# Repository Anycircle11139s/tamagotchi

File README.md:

# tamagotchi
I made a custom tamagotchi for myself because stasis is taking forever to send the tamagotchis and I lowkey gotta improve my responsibility. I followed the guided tutorial from fallout and looked at some other projects for reference. Overall I am really happy with my progress and I learnt a decent amount about PCBs while retaining/honing my CADing skills. The schematic and PCB were fairly easy for me, but when creating the pcb, I decided on makeing the weirdest shape in existence, so I had to spend a really long time matching the PCB shape for the CAD case. The journals and other info can be found on my stasis project (https://stasis.hackclub.com/dashboard/projects/cmoldt6hz000401o6fho5nhdl)
<br>

<br>

<br>

<br>

<br>

<br>

<br>
<br>

# BOM
<br>

|Name            |Purpose                                           |Quantity|Total Cost (USD)|Link                                                                                                                                                                                                                                                                                                                                                                                                                                                                                                                                                                                                                                                                                                                                                       |Distributor|
|----------------|--------------------------------------------------|--------|----------------|-----------------------------------------------------------------------------------------------------------------------------------------------------------------------------------------------------------------------------------------------------------------------------------------------------------------------------------------------------------------------------------------------------------------------------------------------------------------------------------------------------------------------------------------------------------------------------------------------------------------------------------------------------------------------------------------------------------------------------------------------------------|-----------|
|pcb             |the thing that wires and holds everything together|1       |11.53           |                                                                                                                                                                                                                                                                                                                                                                                                                                                                                                                                                                                                                                                                                                                                                           |jlcpcb     |
|Magnets         |to attach sides                                   |1       |4.75            |https://www.aliexpress.com/item/1005009535032247.html?spm=a2g0o.productlist.main.4.4dd7NPjkNPjkv3&aem_p4p_detail=202604300427182822598833874820004345827&algo_pvid=41b06e34-94ed-43cb-b84a-c4fe7c5f9e02&algo_exp_id=41b06e34-94ed-43cb-b84a-c4fe7c5f9e02-3&pdp_ext_f=%7B%22order%22%3A%22105%22%2C%22eval%22%3A%221%22%2C%22fromPage%22%3A%22search%22%7D&pdp_npi=6%40dis%21USD%216.34%214.75%21%21%216.34%214.75%21%402103129017775484388655086e60e7%2112000049390216938%21sea%21AU%217402515296%21X%211%210%21n_tag%3A-29919%3Bd%3Aef1e07f3%3Bm03_new_user%3A-29895&curPageLogUid=tErlM9zdaACY&utparam-url=scene%3Asearch%7Cquery_from%3A%7Cx_object_id%3A1005009535032247%7C_p_origin_prod%3A&search_p4p_id=202604300427182822598833874820004345827_1   |ali express|
|screws          |to screw it together                              |1       |1.19            |https://www.aliexpress.com/item/1005007156753413.html?spm=a2g0o.productlist.main.2.70e1KT6rKT6r4z&algo_pvid=1dca779f-b739-40b3-9bd1-faf88dca4f7c&algo_exp_id=1dca779f-b739-40b3-9bd1-faf88dca4f7c-1&pdp_ext_f=%7B%22order%22%3A%221578%22%2C%22spu_best_type%22%3A%22price%22%2C%22eval%22%3A%221%22%2C%22fromPage%22%3A%22search%22%7D&pdp_npi=6%40dis%21USD%211.08%210.81%21%21%217.33%215.50%21%402101e80317775483140854245e64be%2112000039637096444%21sea%21AU%217402515296%21X%211%210%21n_tag%3A-29919%3Bd%3Aef1e07f3%3Bm03_new_user%3A-29895&curPageLogUid=AvMUevYtYAsq&utparam-url=scene%3Asearch%7Cquery_from%3A%7Cx_object_id%3A1005007156753413%7C_p_origin_prod%3A                                                                             |ali express|
|brass insert nut|screw connecting                                  |1       |1.42            |https://www.aliexpress.com/item/1005008644449489.html?spm=a2g0o.productlist.main.3.78eeZjH4ZjH4OB&algo_pvid=db5c73ed-6ec1-41fe-8986-9bfb1d5b6be5&algo_exp_id=db5c73ed-6ec1-41fe-8986-9bfb1d5b6be5-2&pdp_ext_f=%7B%22order%22%3A%221514%22%2C%22spu_best_type%22%3A%22price%22%2C%22eval%22%3A%221%22%2C%22fromPage%22%3A%22search%22%7D&pdp_npi=6%40dis%21USD%211.34%211.34%21%21%211.34%211.34%21%40210328db17775481559351730e4552%2112000046073221966%21sea%21AU%217402515296%21X%211%210%21n_tag%3A-29919%3Bd%3Aef1e07f3%3Bm03_new_user%3A-29895&curPageLogUid=N0KmBMAkcwau&utparam-url=scene%3Asearch%7Cquery_from%3A%7Cx_object_id%3A1005008644449489%7C_p_origin_prod%3A                                                                             |ali express|
|headers         |connecting stuff                                  |1       |2.20            |https://www.aliexpress.com/item/1005008490007737.html?spm=a2g0o.productlist.main.13.6371zODLzODLx7&utparam-url=scene%3Asearch%7Cquery_from%3Apc_back_same_best%7Cx_object_id%3A1005008490007737%7C_p_origin_prod%3A&algo_pvid=3e176fe8-4a7a-4d31-b79a-1f602f4ac221&algo_exp_id=3e176fe8-4a7a-4d31-b79a-1f602f4ac221&pdp_ext_f=%7B%22order%22%3A%2212%22%2C%22fromPage%22%3A%22search%22%7D&pdp_npi=6%40dis%21USD%214.41%212.20%21%21%2130.04%2115.02%21%4021032f3717775480916557700ea446%2112000046344834123%21sea%21AU%217402515296%21X%211%210%21n_tag%3A-29919%3Bd%3Aef1e07f3%3Bm03_new_user%3A-29895                                                                                                                                                   |ali express|
|rgb led         |backlighting                                      |1       |3.22            |https://www.aliexpress.com/item/1005005340818659.html?spm=a2g0o.productlist.main.2.27ecZnzNZnzNXq&algo_pvid=2a91e50a-e37a-43a0-962a-80c63ca83067&algo_exp_id=2a91e50a-e37a-43a0-962a-80c63ca83067-1&pdp_ext_f=%7B%22order%22%3A%22156%22%2C%22eval%22%3A%221%22%2C%22fromPage%22%3A%22search%22%7D&pdp_npi=6%40dis%21USD%213.79%213.22%21%21%2125.82%2121.95%21%40210318a717775480091197565e929d%2112000032670306832%21sea%21AU%217402515296%21X%211%210%21n_tag%3A-29919%3Bd%3Aef1e07f3%3Bm03_new_user%3A-29895&curPageLogUid=cKOfwHq0NXxX&utparam-url=scene%3Asearch%7Cquery_from%3A%7Cx_object_id%3A1005005340818659%7C_p_origin_prod%3A                                                                                                                |ali express|
|lipo battery    |to power the tamagotchi                           |1       |3.87            |https://www.aliexpress.com/item/1005006995943957.html?spm=a2g0o.productlist.main.2.5f5dSSeISSeIAA&algo_pvid=465d721f-19a4-45c9-a5c9-23c479530c8c&algo_exp_id=465d721f-19a4-45c9-a5c9-23c479530c8c-1&pdp_ext_f=%7B%22order%22%3A%2269%22%2C%22eval%22%3A%221%22%2C%22fromPage%22%3A%22search%22%7D&pdp_npi=6%40dis%21USD%213.99%213.87%21%21%213.99%213.87%21%402101dedf17775479461817954ee138%2112000038987399864%21sea%21AU%217402515296%21X%211%210%21n_tag%3A-29919%3Bd%3Aef1e07f3%3Bm03_new_user%3A-29895&curPageLogUid=hirB6cYhLl1Y&utparam-url=scene%3Asearch%7Cquery_from%3A%7Cx_object_id%3A1005006995943957%7C_p_origin_prod%3A                                                                                                                   |ali express|
|buzzer          |noise creating                                    |1       |3.72            |https://www.aliexpress.com/item/1005010498958481.html?spm=a2g0o.productlist.main.1.76bdfcs9fcs9P3&algo_pvid=34f672fb-7ef5-4735-89ca-ae9c4020e3eb&algo_exp_id=34f672fb-7ef5-4735-89ca-ae9c4020e3eb-0&pdp_ext_f=%7B%22order%22%3A%2263%22%2C%22eval%22%3A%221%22%2C%22fromPage%22%3A%22search%22%7D&pdp_npi=6%40dis%21USD%218.08%213.72%21%21%2154.98%2125.29%21%402103212317775478502967329e6f35%2112000052601560955%21sea%21AU%217402515296%21X%211%210%21n_tag%3A-29919%3Bd%3Aef1e07f3%3Bm03_new_user%3A-29895&curPageLogUid=TC8xco9BnyGL&utparam-url=scene%3Asearch%7Cquery_from%3A%7Cx_object_id%3A1005010498958481%7C_p_origin_prod%3A                                                                                                                 |ali express|
|tactile buttons |the buttons for the tamagotchi                    |1       |2.77            |https://www.aliexpress.com/item/1005006477792707.html?spm=a2g0o.productlist.main.4.1c40fds0fds0x5&algo_pvid=3fbefc71-927e-4d72-a400-6fba258fd7be&aem_p4p_detail=2026043004152918909141188223480004376545&algo_exp_id=3fbefc71-927e-4d72-a400-6fba258fd7be-3&pdp_ext_f=%7B%22order%22%3A%2272%22%2C%22eval%22%3A%221%22%2C%22fromPage%22%3A%22search%22%7D&pdp_npi=6%40dis%21USD%212.77%212.77%21%21%2118.88%2118.88%21%402101e81117775477298928142e09f2%2112000037345527687%21sea%21AU%217402515296%21X%211%210%21n_tag%3A-29919%3Bd%3Aef1e07f3%3Bm03_new_user%3A-29895&curPageLogUid=oOi1vD6X5cbm&utparam-url=scene%3Asearch%7Cquery_from%3A%7Cx_object_id%3A1005006477792707%7C_p_origin_prod%3A&search_p4p_id=2026043004152918909141188223480004376545_1|ali express|
|oled display    |the screen for tamagotchi                         |1       |3.63            |https://www.aliexpress.com/item/1005010183965559.html?spm=a2g0o.productlist.main.2.34238INy8INymB&algo_pvid=bec8d602-9698-47c4-a758-c833280b8ff4&algo_exp_id=bec8d602-9698-47c4-a758-c833280b8ff4-1&pdp_ext_f=%7B%22order%22%3A%22122%22%2C%22eval%22%3A%221%22%2C%22fromPage%22%3A%22search%22%7D&pdp_npi=6%40dis%21USD%217.72%213.63%21%21%2152.52%2124.68%21%402101d97817775476210582621e1e3e%2112000051437252682%21sea%21AU%217402515296%21X%211%210%21n_tag%3A-29919%3Bd%3Aef1e07f3%3Bm03_new_user%3A-29895&curPageLogUid=zOt9Pu2duZKz&utparam-url=scene%3Asearch%7Cquery_from%3A%7Cx_object_id%3A1005010183965559%7C_p_origin_prod%3A                                                                                                                |ali express|
|xiao esp32 c3   |microcontroller                                   |1       |8.73            |https://www.aliexpress.com/item/1005007084388623.html?spm=a2g0o.productlist.main.6.7ff17845JaPUsy&algo_pvid=b6a30a8c-5e3b-49d2-abaf-5319d65d130d&algo_exp_id=b6a30a8c-5e3b-49d2-abaf-5319d65d130d-11&pdp_ext_f=%7B%22order%22%3A%221743%22%2C%22spu_best_type%22%3A%22price%22%2C%22eval%22%3A%221%22%2C%22fromPage%22%3A%22search%22%7D&pdp_npi=6%40dis%21USD%218.73%218.73%21%21%2159.43%2159.43%21%402101d6fe17775475072146368e0a78%2112000056349597200%21sea%21AU%217402515296%21X%211%210%21n_tag%3A-29919%3Bd%3Aef1e07f3%3Bm03_new_user%3A-29895&curPageLogUid=dgDA2Lb7IDfr&utparam-url=scene%3Asearch%7Cquery_from%3A%7Cx_object_id%3A1005007084388623%7C_p_origin_prod%3A                                                                          |ali express|

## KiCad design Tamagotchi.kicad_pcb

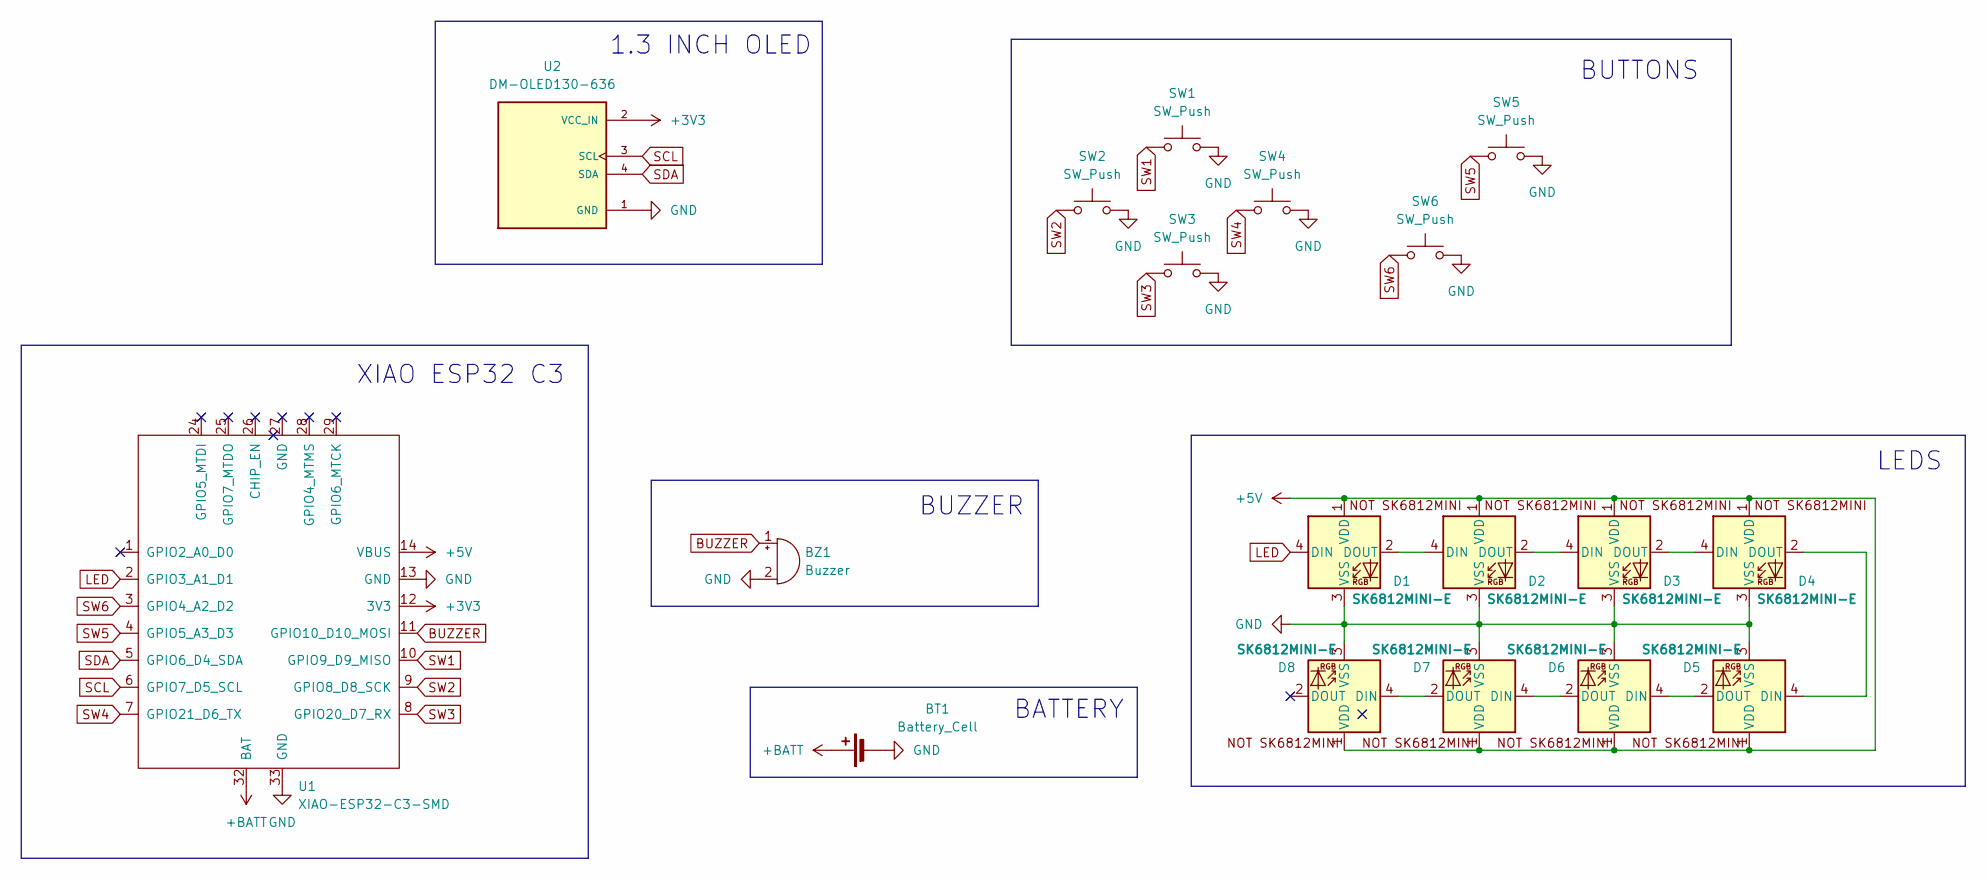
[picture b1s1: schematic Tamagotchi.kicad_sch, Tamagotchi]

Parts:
BT1: Battery_Cell; PinHeader_1x02_P2.54mm_Vertical
BZ1: Buzzer; Buzzer_12x9.5RM7.6
D1, D2, D3, D4, D5, D6, D7, D8: SK6812MINI-E; SK6812MINI-E_fixed
SW1, SW2, SW3, SW4, SW5, SW6: SW_Push; SW_VS-1213-67-160GF
U1: XIAO-ESP32-C3-SMD; XIAO-ESP32-C3-DIP-SMD
U2: DM-OLED130-636; LCD_OLED_128X64_1.3_I2C; PARTREV 2018-09-10

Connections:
+3V3: U1.12 (3V3), U2.2 (VCC_IN)
+5V: D1.1 (VDD), D2.1 (VDD), D3.1 (VDD), D4.1 (VDD), D5.1 (VDD), D6.1 (VDD), D7.1 (VDD), D8.1 (VDD), U1.14 (VBUS)
+BATT: BT1.1 (+), U1.32 (BAT)
BUZZER: BZ1.1 (+), U1.11 (GPIO10_D10_MOSI)
GND: BT1.2 (-), BZ1.2 (-), D1.3 (VSS), D2.3 (VSS), D3.3 (VSS), D4.3 (VSS), D5.3 (VSS), D6.3 (VSS), D7.3 (VSS), D8.3 (VSS), SW1.2, SW2.2, SW3.2, SW4.2, SW5.2, SW6.2, U1.13 (GND), U1.33 (GND), U2.1 (GND)
LED: D1.4 (DIN), U1.2 (GPIO3_A1_D1)
unnamed: D1.2 (DOUT), D2.4 (DIN)
unnamed: D2.2 (DOUT), D3.4 (DIN)
unnamed: D3.2 (DOUT), D4.4 (DIN)
unnamed: D4.2 (DOUT), D5.4 (DIN)
unnamed: D5.2 (DOUT), D6.4 (DIN)
unnamed: D6.2 (DOUT), D7.4 (DIN)
unnamed: D7.2 (DOUT), D8.4 (DIN)
SCL: U1.6 (GPIO7_D5_SCL), U2.3 (SCL)
SDA: U1.5 (GPIO6_D4_SDA), U2.4 (SDA)
SW1: SW1.1, U1.10 (GPIO9_D9_MISO)
SW2: SW2.1, U1.9 (GPIO8_D8_SCK)
SW3: SW3.1, U1.8 (GPIO20_D7_RX)
SW4: SW4.1, U1.7 (GPIO21_D6_TX)
SW5: SW5.1, U1.4 (GPIO5_A3_D3)
SW6: SW6.1, U1.3 (GPIO4_A2_D2)

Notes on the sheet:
1.3 INCH OLED
BUTTONS
BUZZER
XIAO ESP32 C3
BATTERY
LEDS

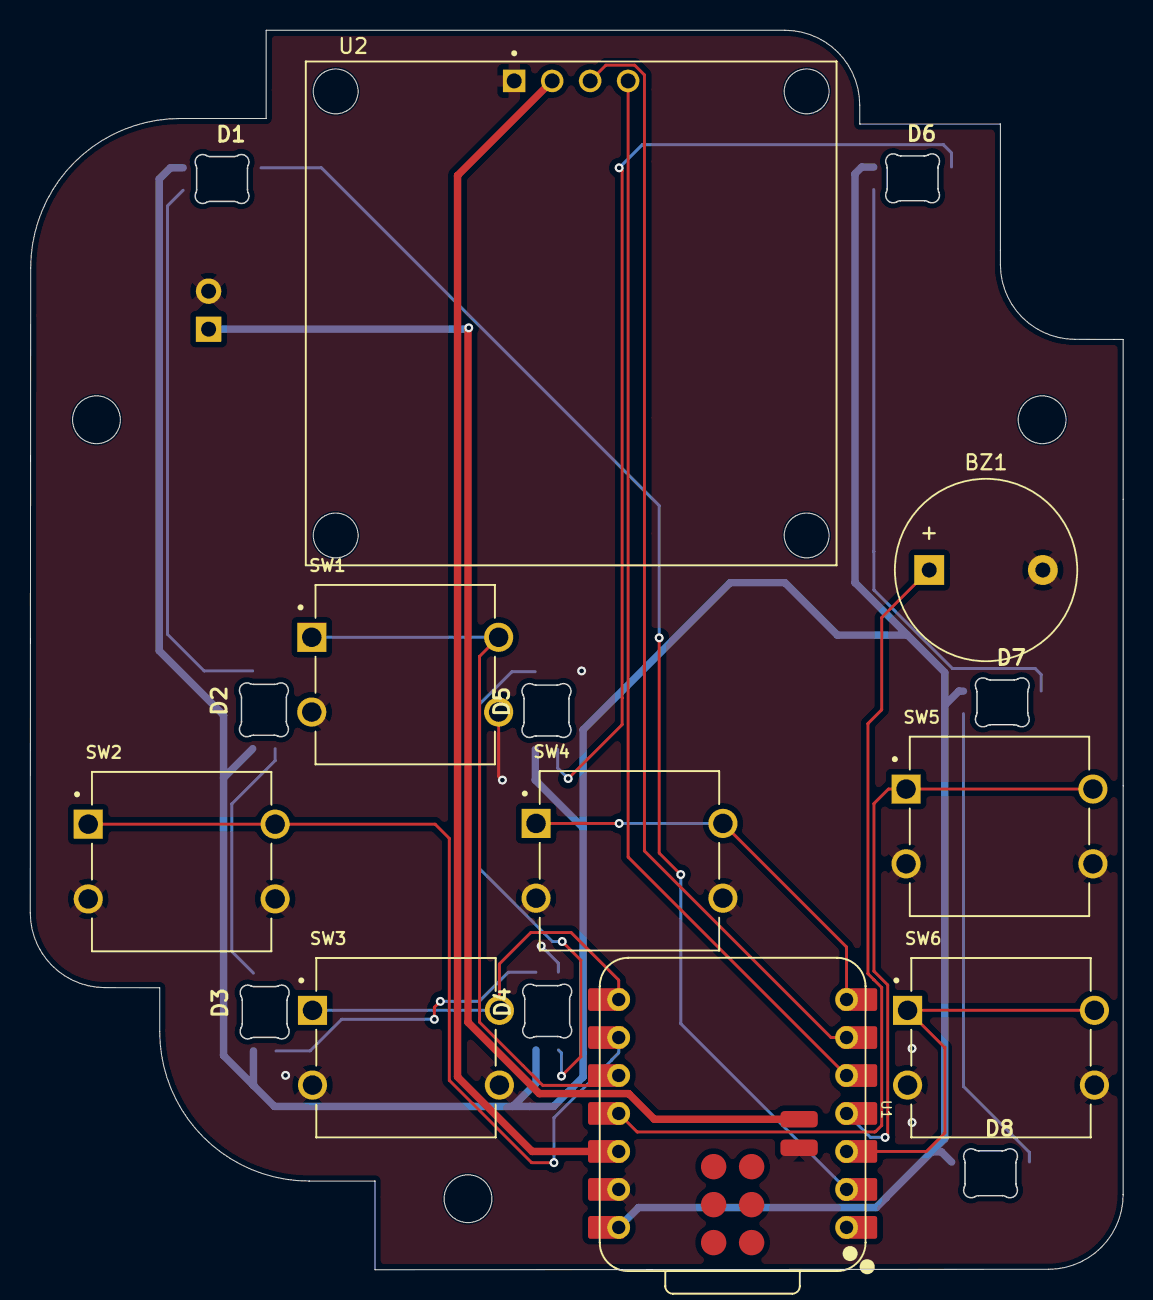
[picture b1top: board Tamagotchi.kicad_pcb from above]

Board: 2 copper layers, 73.1 x 82.9 mm, 18 parts (1 on the bottom side), 21 nets.
